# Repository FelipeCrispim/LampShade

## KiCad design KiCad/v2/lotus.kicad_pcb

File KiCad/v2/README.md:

ESP-12 module: http://cholla.mmto.org/esp8266/esp12/

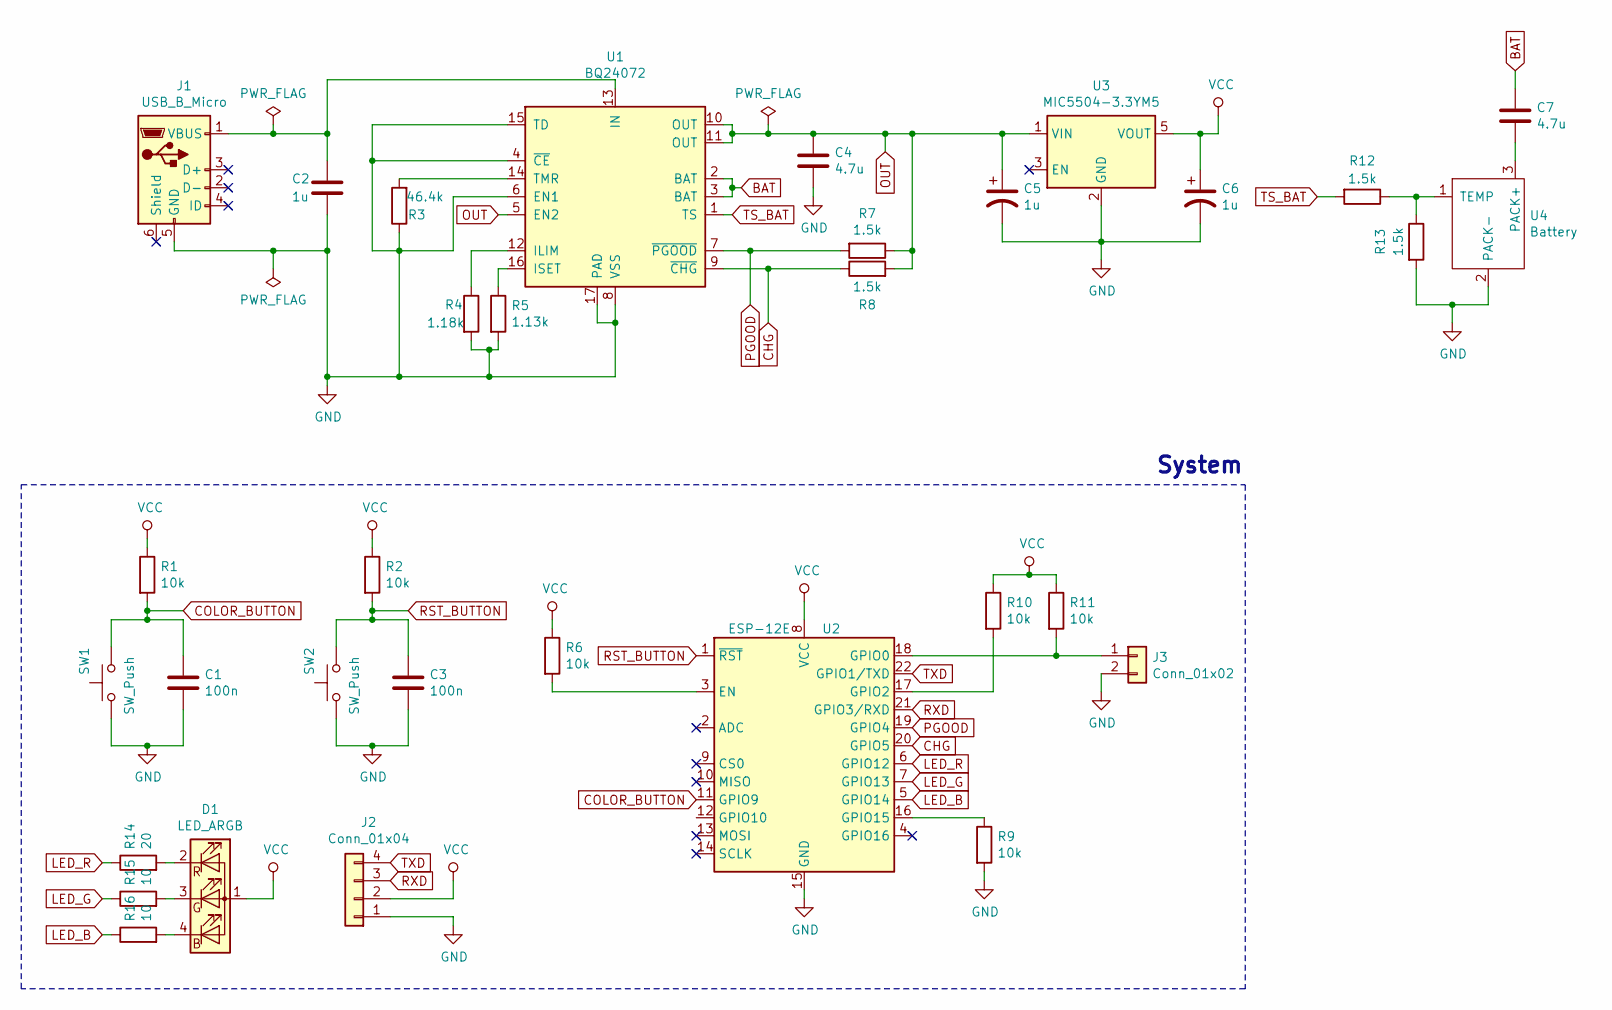
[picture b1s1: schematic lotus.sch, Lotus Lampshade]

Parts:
C1, C3: 100n; C_0402_1005Metric
C2: 1u; C_0402_1005Metric
C4, C7: 4.7u; C_0402_1005Metric
C5, C6: 1u; CP_EIA-3216-18_Kemet-A
D1: LED_ARGB; LED_Cree-PLCC4_3.2x2.8mm_CCW
J1: USB_B_Micro; USB_Micro-B_Molex_47346-0001
J2: Conn_01x04; PinHeader_1x04_P2.54mm_Vertical
J3: Conn_01x02; PinHeader_1x02_P2.54mm_Vertical
R1, R2, R6, R9, R10, R11: 10k; R_0402_1005Metric
R3: 46.4k; R_0402_1005Metric
R4: 1.18k; R_0402_1005Metric
R5: 1.13k; R_0402_1005Metric
R7, R8, R12, R13: 1.5k; R_0402_1005Metric
R14: 20; R_0402_1005Metric
R15, R16: 10; R_0402_1005Metric
SW1: SW_Push; SW_Tactile_SPST_Angled_PTS645Vx58-2LFS
SW2: SW_Push; SW_PUSH_6mm
U1: BQ24072; QFN-16-1EP_3x3mm_P0.5mm_EP1.8x1.8mm
U2: ESP-12E
U3: MIC5504-3.3YM5; SOT-23-5
U4: Battery; PinHeader_1x03_P2.54mm_Vertical

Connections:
BAT: C7.1, U1.2 (BAT), U1.3 (BAT)
CHG: R8.1, U1.9 (~CHG), U2.20 (GPIO5)
COLOR_BUTTON: C1.1, R1.2, SW1.2, U2.11 (GPIO9)
GND: C1.2, C2.2, C3.2, C4.2, C5.2, C6.2, J1.5 (GND), J2.1, J3.2, R3.1, R4.2, R5.2, R9.2, R13.2, SW1.1, SW2.1, U1.4 (~CE), U1.6 (EN1), U1.8 (VSS), U1.15 (TD), U1.17 (PAD), U2.15 (GND), U3.2 (GND), U4.2 (PACK-)
LED_B: R16.1, U2.5 (GPIO14)
LED_G: R15.1, U2.7 (GPIO13)
LED_R: R14.1, U2.6 (GPIO12)
unnamed: C2.1, J1.1 (VBUS), U1.13 (IN)
unnamed: C7.2, U4.3 (PACK+)
unnamed: D1.2 (RK), R14.2
unnamed: D1.3 (GK), R15.2
unnamed: D1.4 (BK), R16.2
unnamed: J3.1, R11.2, U2.18 (GPIO0)
unnamed: R3.2, U1.14 (TMR)
unnamed: R4.1, U1.12 (ILIM)
unnamed: R5.1, U1.16 (ISET)
unnamed: R6.2, U2.3 (EN)
unnamed: R9.1, U2.16 (GPIO15)
unnamed: R10.2, U2.17 (GPIO2)
unnamed: R12.1, R13.1, U4.1 (TEMP)
OUT: C4.1, C5.1, R7.1, R8.2, U1.5 (EN2), U1.10 (OUT), U1.11 (OUT), U3.1 (VIN)
PGOOD: R7.2, U1.7 (~PGOOD), U2.19 (GPIO4)
RST_BUTTON: C3.1, R2.2, SW2.2, U2.1 (~RST)
RXD: J2.3, U2.21 (GPIO3/RXD)
TS_BAT: R12.2, U1.1 (TS)
TXD: J2.4, U2.22 (GPIO1/TXD)
VCC: C6.1, D1.1 (A), J2.2, R1.1, R2.1, R6.1, R10.1, R11.1, U2.8 (VCC), U3.5 (VOUT)

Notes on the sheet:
System

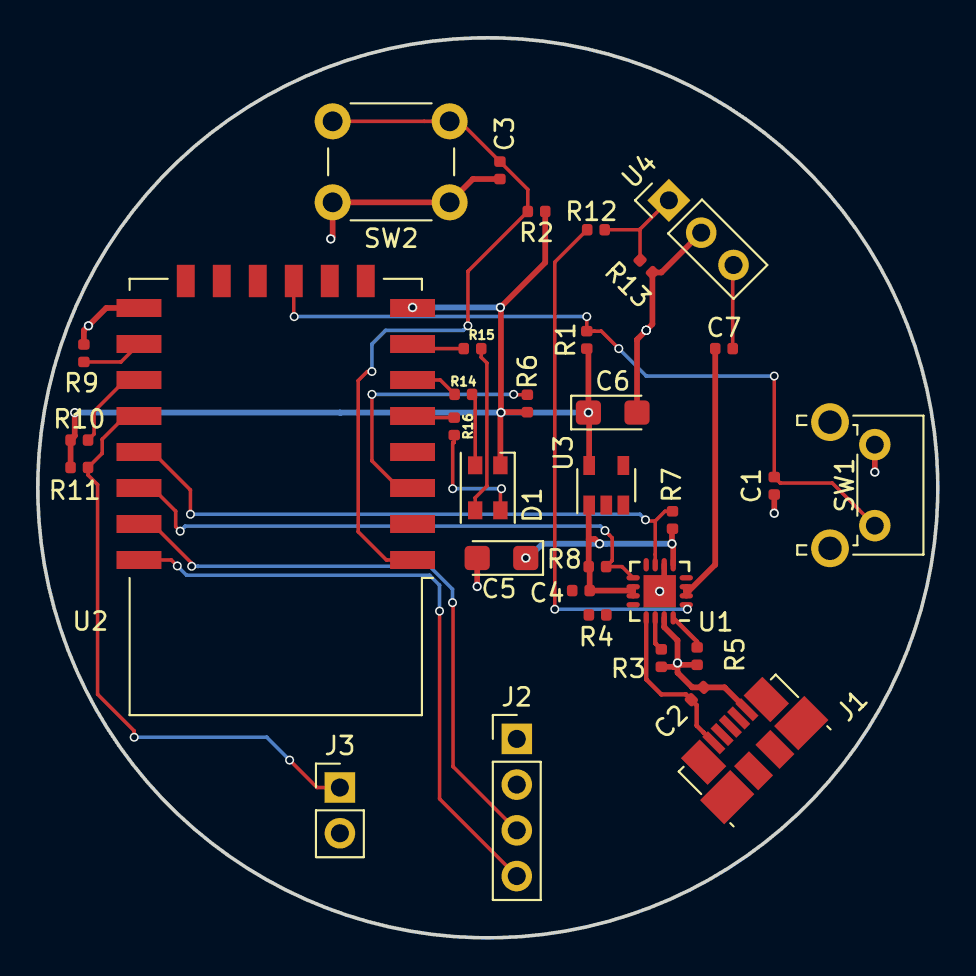
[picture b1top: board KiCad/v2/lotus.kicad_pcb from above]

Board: 2 copper layers, 50.0 x 50.0 mm, 33 parts (0 on the bottom side), 27 nets.

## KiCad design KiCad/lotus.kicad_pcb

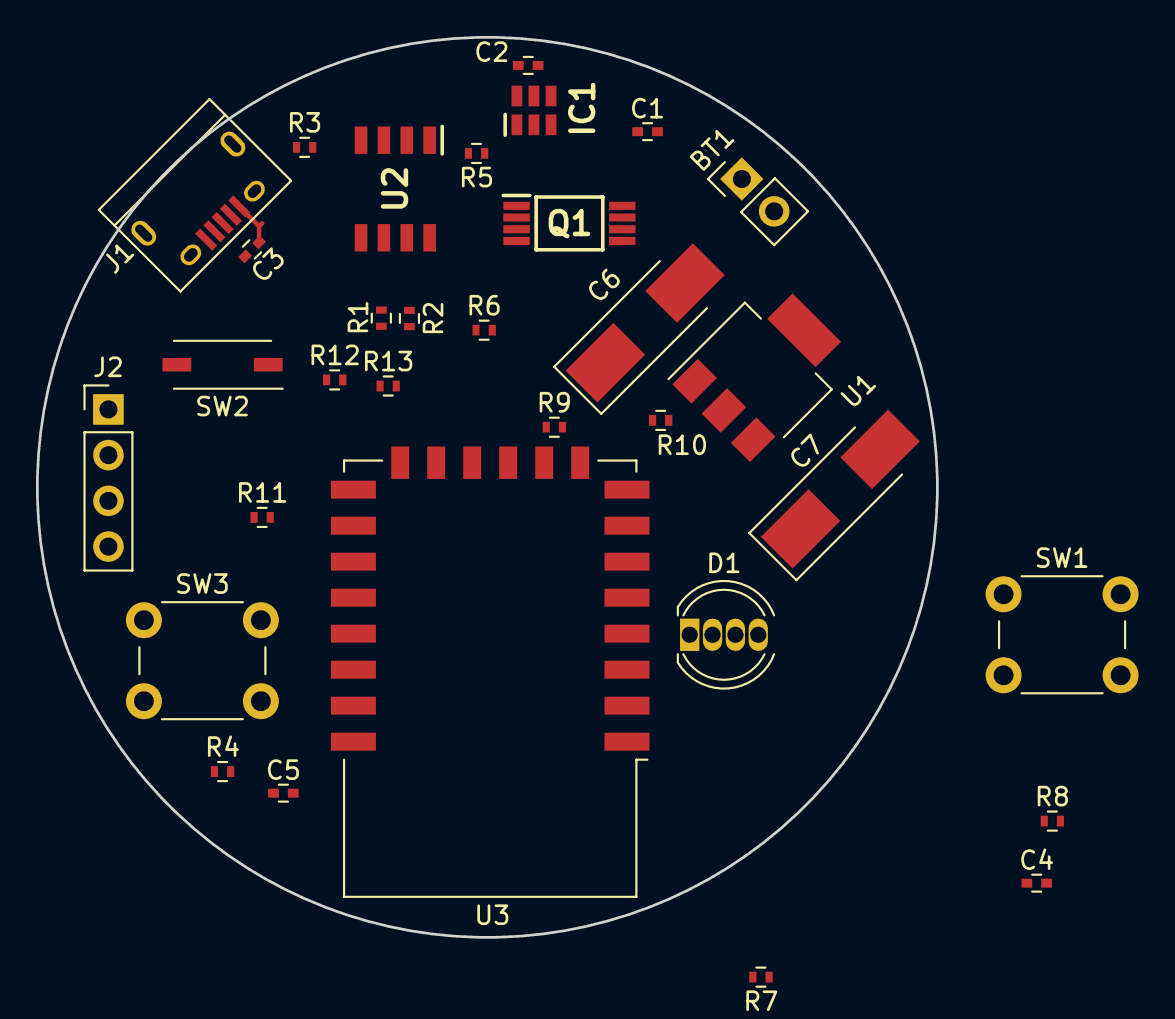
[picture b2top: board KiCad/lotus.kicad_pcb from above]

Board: 2 copper layers, 50.0 x 50.0 mm, 32 parts (0 on the bottom side), 25 nets.

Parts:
BT1: Battery_Cell; Pin_Header_Straight_1x02_Pitch2.54mm
C1: 10u; C_0402
C2, C3: 0.1u; C_0402
C4, C5: 100n; C_0402
C6: 100n; CP_Tantalum_Case-C_EIA-6032-28_Hand
C7: 10u; CP_Tantalum_Case-C_EIA-6032-28_Hand
D1: LED_ARGB; LED_D5.0mm-4
IC1: DW01A-G; SOT95P190X145-6N
J1: USB_OTG; USB_Micro-B
J2: FTDI; Pin_Header_Straight_1x04_Pitch2.54mm
Q1: FS8205A; SOP65P640X120-8N
R1, R2, R6: 1k; R_0402
R3: 1.2k; R_0402
R4, R7, R8, R9, R10, R11, R12, R13: 10k; R_0402
R5: 100; R_0402
SW1, SW3: SW_Push; SW_PUSH_6mm
SW2: SW_DIP_x01; SW_DIP_x1_W5.08mm_Slide_Copal_CHS-A
U1: LD1117S33CTR; SOT-223
U2: TP4056
U3: ESP-12E

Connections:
GND: C1.2, C3.2, C4.1, C5.1, C6.2, C7.2, J1.5, J2.1, Q1.6, Q1.7, R3.2, R6.2, R9.2, SW1.1, SW2.2, SW3.1, U1.1, U2.1, U2.3, U3.9
LED_BUTTON: C5.2, R4.2, SW3.2, U3.19
unnamed: BT1.1, C1.1, C6.1, R5.1, U1.3, U2.5
unnamed: BT1.2, C2.1, IC1.6, Q1.2, Q1.3
unnamed: C2.2, IC1.5, R5.2
unnamed: C3.1, J1.1, U2.4, U2.8
unnamed: IC1.1, Q1.4
unnamed: IC1.2, R6.1
unnamed: IC1.3, Q1.5
unnamed: R1.1, U2.6
unnamed: R2.1, U2.7
unnamed: R3.1, U2.2
unnamed: R7.2, U3.3
unnamed: R9.1, U3.10
unnamed: R10.2, U3.11
unnamed: R11.1, SW2.1, U3.12
REST_BUTTON: C4.2, R8.2, SW1.2, U3.1
RXD: J2.3, U3.15
TXD: J2.4, U3.16
VCC: C7.1, D1.1, J2.2, R4.1, R7.1, R8.1, R10.1, R11.2, R12.1, R13.1, U1.2, U3.8
led_b: D1.4, U3.6
led_g: D1.3, U3.5
led_r: D1.2, U3.4
pin_chrg: R2.2, R13.2, U3.13
pin_stdby: R1.2, R12.2, U3.14

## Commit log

2018-03-15 Primeiro commit
2018-04-02 Adicionado código arduino
2018-04-27 Criado projeto do KiCad
2018-05-03 Atualizado esquemático no KiCad
2018-05-08 Adicionado footprints
2018-05-08 Terminado definição dos footprints
2018-05-09 Organizado footprints no PCB
2018-10-10 Criado versão 2 do projeto no kicad
2018-11-02 Atualizado versão 2
2018-11-18 Adicionado bateria no esquemático v2
2018-11-20 Mudado regulador de tensão
2018-11-22 Adicionado alguns footprints
2018-11-24 Adicionado footprint dos botões, da bateria e dos conectores
2018-12-03 Atualizado footprints
2018-12-03 Começado a criar trilhas no PCB
2018-12-04 Organizado PCB
2018-12-05 Adicionado resistores no led
2020-03-18 Adicionado nome do módulo na referência
